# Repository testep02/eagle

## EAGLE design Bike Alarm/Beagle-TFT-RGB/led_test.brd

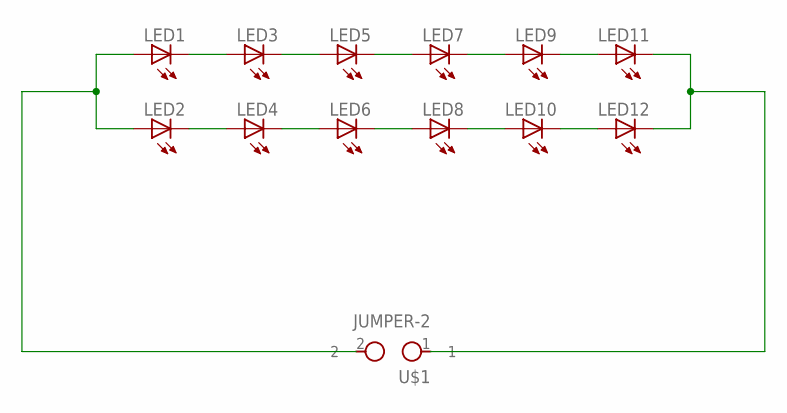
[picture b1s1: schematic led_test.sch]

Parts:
LED1, LED2, LED3, LED4, LED5, LED6, LED7, LED8, LED9, LED10, LED11, LED12: LEDCHIPLED_0603; CHIPLED_0603
U$1: JUMPER-2; 1X02

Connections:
LED+: LED1.A, LED2.A, U$1.2
LED-: LED11.C, LED12.C, U$1.1
unnamed: LED1.C, LED3.A
unnamed: LED3.C, LED5.A
unnamed: LED5.C, LED7.A
unnamed: LED7.C, LED9.A
unnamed: LED9.C, LED11.A
unnamed: LED10.C, LED12.A
unnamed: LED8.C, LED10.A
unnamed: LED6.C, LED8.A
unnamed: LED4.C, LED6.A
unnamed: LED2.C, LED4.A

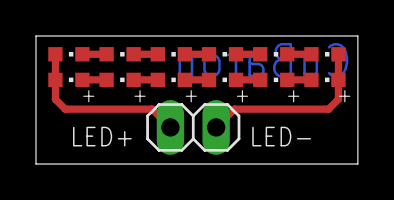
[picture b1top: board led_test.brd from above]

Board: 2 copper layers, 17.9 x 7.1 mm, 13 parts (0 on the bottom side), 12 nets.

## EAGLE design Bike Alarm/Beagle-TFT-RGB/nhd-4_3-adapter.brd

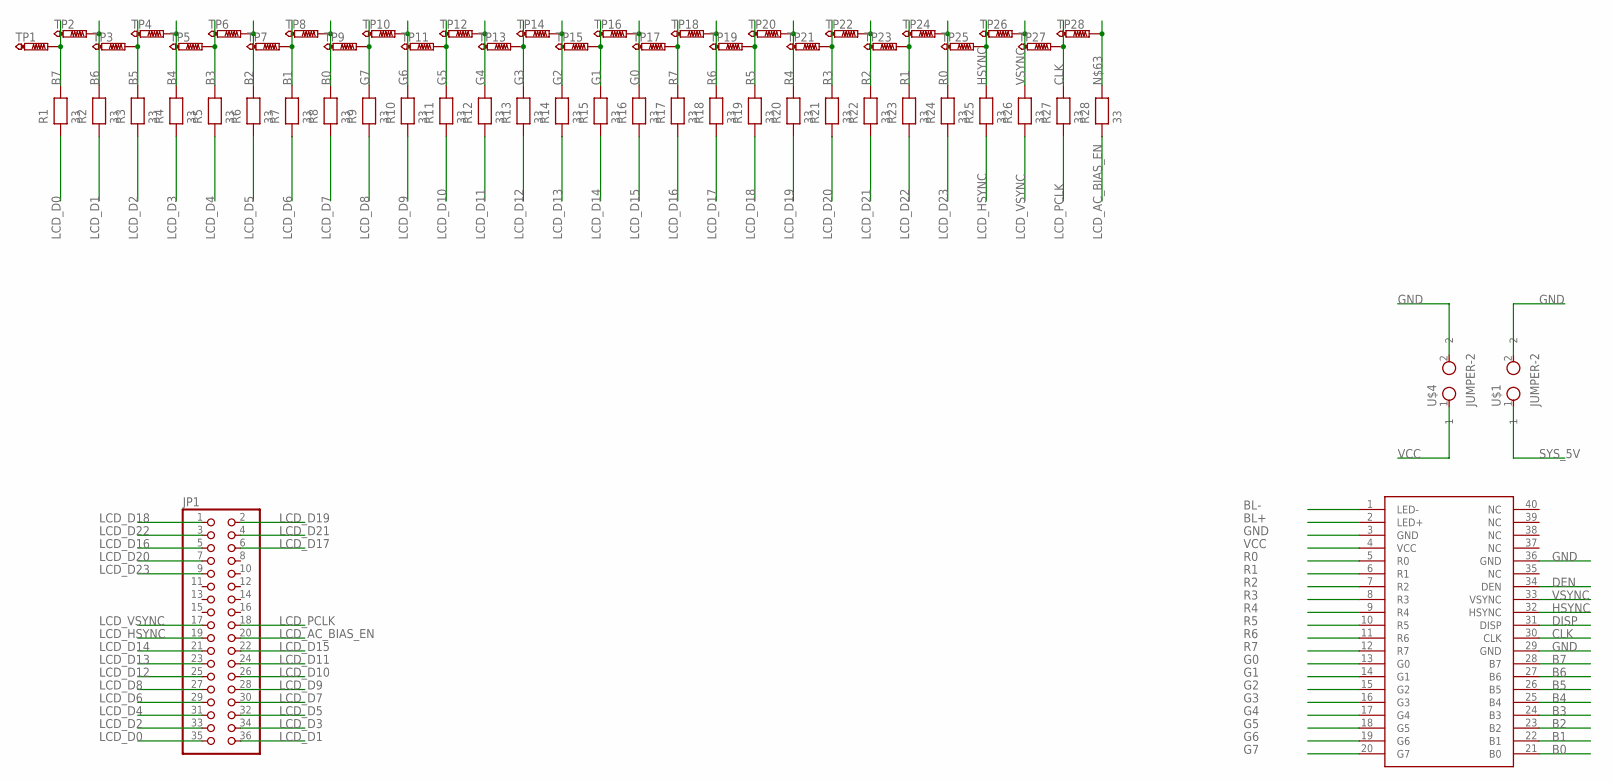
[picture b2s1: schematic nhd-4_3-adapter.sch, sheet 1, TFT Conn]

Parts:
JP1: PINHD-2X18_2.54; 2X18
R1, R2, R3, R4, R5, R6, R7, R8, R9, R10, R11, R12, R13, R14, R15, R16, R17, R18, R19, R20, R21, R22, R23, R24, R25, R26, R27, R28: 33; R0402
TFT1: NHD-4.3-480272EF-ATXL; 40-PIN_SMD
TP1, TP2, TP3, TP4, TP5, TP6, TP7, TP8, TP9, TP10, TP11, TP12, TP13, TP14, TP15, TP16, TP17, TP18, TP19, TP20, TP21, TP22, TP23, TP24, TP25, TP26, TP27, TP28: TESTPAD_PTR1TP06R; TESTPAD_TP06R
U$1, U$4: JUMPER-2; 1X02

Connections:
B0: R8.P$2, TFT1.21 (B0), TP8.TP
B1: R7.P$2, TFT1.22 (B1), TP7.TP
B2: R6.P$2, TFT1.23 (B2), TP6.TP
B3: R5.P$2, TFT1.24 (B3), TP5.TP
B4: R4.P$2, TFT1.25 (B4), TP4.TP
B5: R3.P$2, TFT1.26 (B5), TP3.TP
B6: R2.P$2, TFT1.27 (B6), TP2.TP
B7: R1.P$2, TFT1.28 (B7), TP1.TP
BL+: TFT1.2 (LED+); also elsewhere on the board
BL-: TFT1.1 (LED-); also elsewhere on the board
CLK: R27.P$2, TFT1.30 (CLK), TP27.TP
DEN: TFT1.34 (DEN)
DISP: TFT1.31 (DISP)
G0: R16.P$2, TFT1.13 (G0), TP16.TP
G1: R15.P$2, TFT1.14 (G1), TP15.TP
G2: R14.P$2, TFT1.15 (G2), TP14.TP
G3: R13.P$2, TFT1.16 (G3), TP13.TP
G4: R12.P$2, TFT1.17 (G4), TP12.TP
G5: R11.P$2, TFT1.18 (G5), TP11.TP
G6: R10.P$2, TFT1.19 (G6), TP10.TP
G7: R9.P$2, TFT1.20 (G7), TP9.TP
GND: TFT1.3 (GND), TFT1.29 (GND), TFT1.36 (GND), U$1.2, U$4.2; also elsewhere on the board
HSYNC: R25.P$2, TFT1.32 (HSYNC), TP25.TP
LCD_AC_BIAS_EN: JP1.20, R28.P$1
LCD_D0: JP1.35, R1.P$1
LCD_D1: JP1.36, R2.P$1
LCD_D2: JP1.33, R3.P$1
LCD_D3: JP1.34, R4.P$1
LCD_D4: JP1.31, R5.P$1
LCD_D5: JP1.32, R6.P$1
LCD_D6: JP1.29, R7.P$1
LCD_D7: JP1.30, R8.P$1
LCD_D8: JP1.27, R9.P$1
LCD_D9: JP1.28, R10.P$1
LCD_D10: JP1.26, R11.P$1
LCD_D11: JP1.24, R12.P$1
LCD_D12: JP1.25, R13.P$1
LCD_D13: JP1.23, R14.P$1
LCD_D14: JP1.21, R15.P$1
LCD_D15: JP1.22, R16.P$1
LCD_D16: JP1.5, R17.P$1
LCD_D17: JP1.6, R18.P$1
LCD_D18: JP1.1, R19.P$1
LCD_D19: JP1.2, R20.P$1
LCD_D20: JP1.7, R21.P$1
LCD_D21: JP1.4, R22.P$1
LCD_D22: JP1.3, R23.P$1
LCD_D23: JP1.9, R24.P$1
LCD_HSYNC: JP1.19, R25.P$1
LCD_PCLK: JP1.18, R27.P$1
LCD_VSYNC: JP1.17, R26.P$1
unnamed: R28.P$2, TP28.TP
R0: R24.P$2, TFT1.5 (R0), TP24.TP
R1: R23.P$2, TFT1.6 (R1), TP23.TP
R2: R22.P$2, TFT1.7 (R2), TP22.TP
R3: R21.P$2, TFT1.8 (R3), TP21.TP
R4: R20.P$2, TFT1.9 (R4), TP20.TP
R5: R19.P$2, TFT1.10 (R5), TP19.TP
R6: R18.P$2, TFT1.11 (R6), TP18.TP
R7: R17.P$2, TFT1.12 (R7), TP17.TP
SYS_5V: U$1.1; also elsewhere on the board
VCC: TFT1.4 (VCC), U$4.1; also elsewhere on the board
VSYNC: R26.P$2, TFT1.33 (VSYNC), TP26.TP

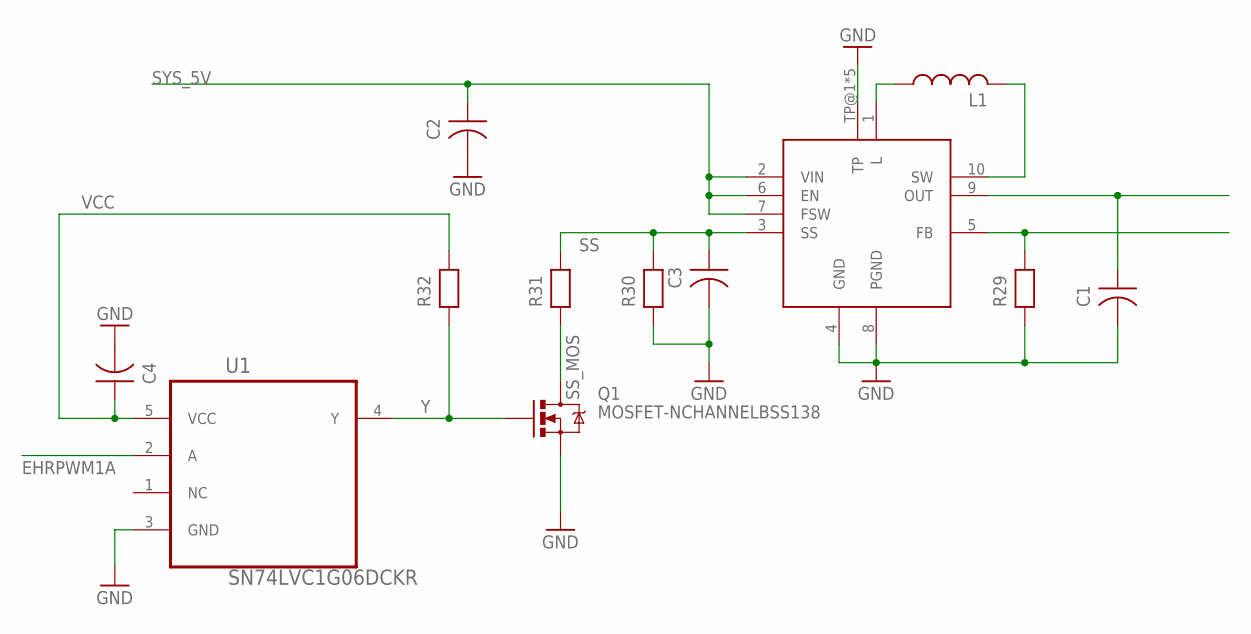
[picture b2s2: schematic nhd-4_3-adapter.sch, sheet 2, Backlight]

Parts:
C1, C2: PCAP0805LEVEL3; R0805
C3, C4: PCAP0603LEVEL3; R0603
L1: L-US; VLCF4018-2
Q1: MOSFET-NCHANNELBSS138; SOT23
R29, R30, R31, R32: PRES0603LEVEL3; R0603
U1: SN74LVC1G06DCKR; SOT65P210X110-5N
U$2: TPS61080; VSON-10

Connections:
BL+: C1.P$2, U$2.9 (OUT); also elsewhere on the board
BL-: R29.P$2, U$2.5 (FB); also elsewhere on the board
EHRPWM1A: U1.2 (A)
GND: C1.P$1, C2.P$1, C3.P$1, C4.P$1, Q1.2 (S), R29.P$1, R30.P$1, U1.3 (GND), U$2.4 (GND), U$2.8 (PGND), U$2.TP@1 (TP), U$2.TP@2 (TP), U$2.TP@3 (TP), U$2.TP@4 (TP), U$2.TP@5 (TP); also elsewhere on the board
L: L1.1, U$2.1 (L)
SS: C3.P$2, R30.P$2, R31.P$2, U$2.3 (SS)
SS_MOS: Q1.3 (D), R31.P$1
SW: L1.2, U$2.10 (SW)
SYS_5V: C2.P$2, U$2.2 (VIN), U$2.6 (EN), U$2.7 (FSW); also elsewhere on the board
VCC: C4.P$2, R32.P$2, U1.5 (VCC); also elsewhere on the board
Y: Q1.1 (G), R32.P$1, U1.4 (Y)

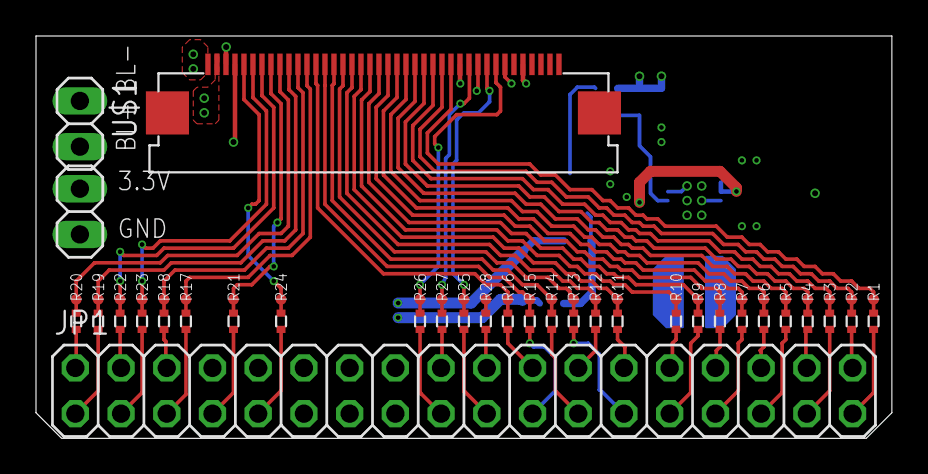
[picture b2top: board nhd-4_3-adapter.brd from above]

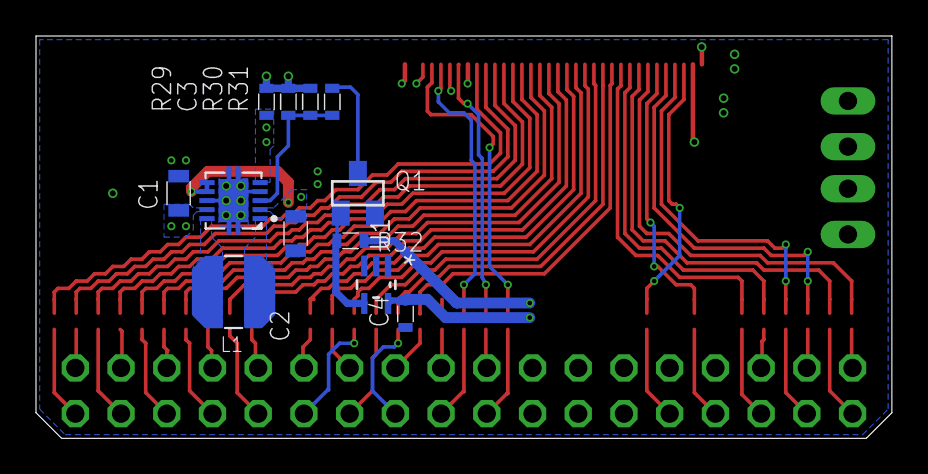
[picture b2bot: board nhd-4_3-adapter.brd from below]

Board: 4 copper layers, 47.5 x 22.4 mm, 72 parts (12 on the bottom side), 66 nets.

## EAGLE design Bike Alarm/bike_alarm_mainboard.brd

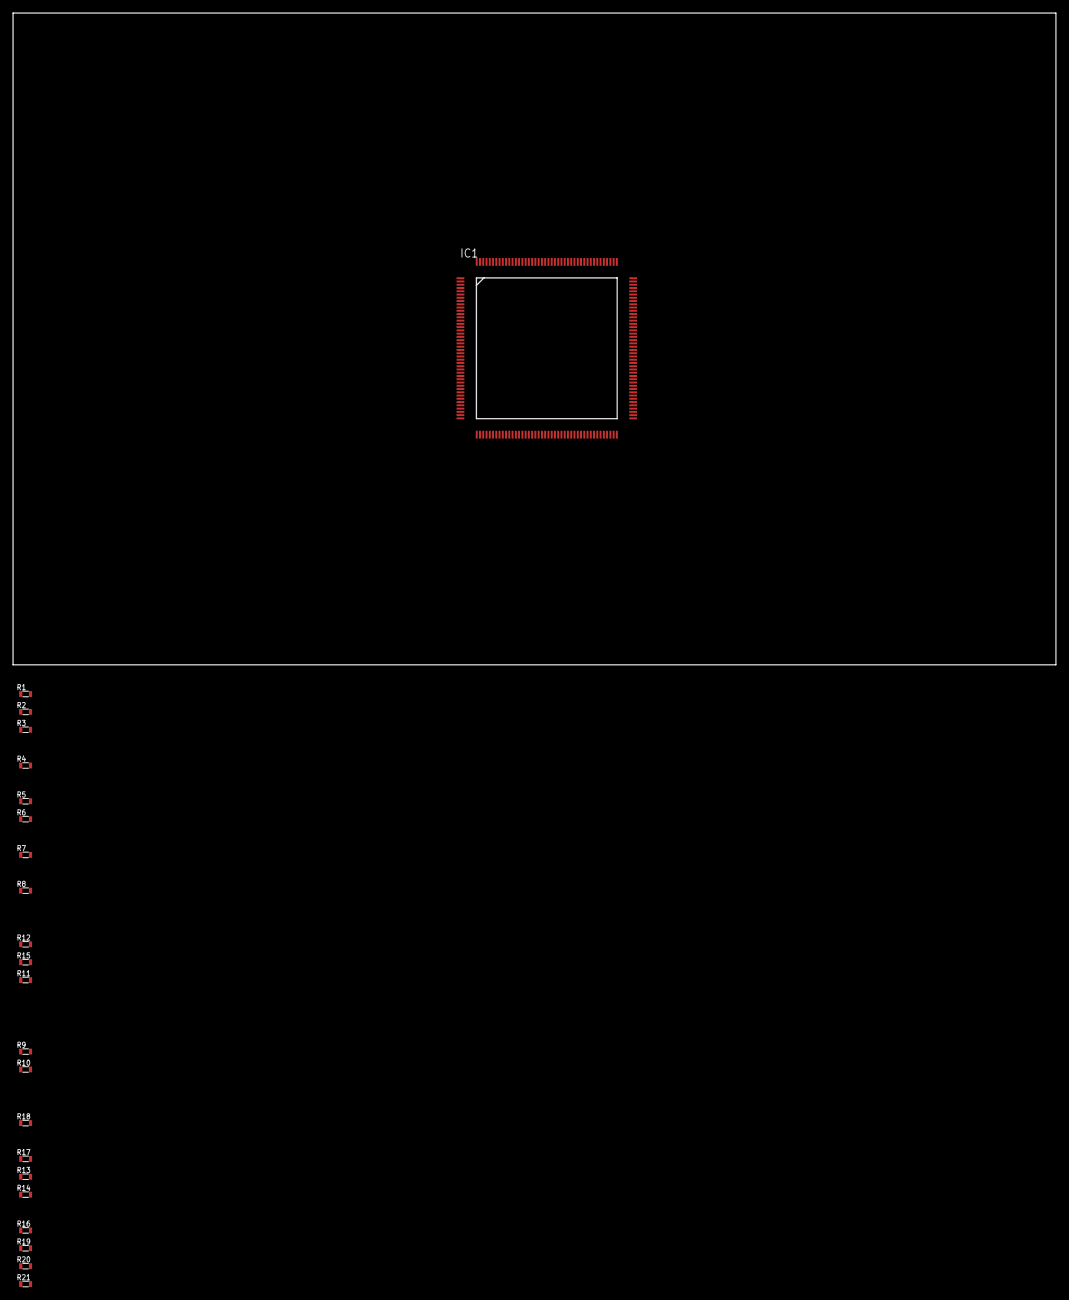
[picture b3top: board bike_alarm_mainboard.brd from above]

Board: 4 copper layers, 160.0 x 100.0 mm, 22 parts (0 on the bottom side), 2 nets, no tracks yet.

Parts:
IC1: STM32F439IIT_STM32F439IIT; STM32F439IIT_LQFP-176
R1, R2, R3, R4, R5, R6, R7, R8, R9, R10, R11, R12, R13, R14, R15, R16, R17, R18, R19, R20, R21: 0603L3

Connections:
VDD: IC1.15, IC1.23, IC1.36, IC1.49, IC1.72, IC1.82, IC1.91, IC1.103, IC1.114, IC1.127, IC1.136, IC1.149, IC1.159, IC1.172
VSS: IC1.14, IC1.22, IC1.61, IC1.71, IC1.90, IC1.102, IC1.113, IC1.126, IC1.135, IC1.148, IC1.158

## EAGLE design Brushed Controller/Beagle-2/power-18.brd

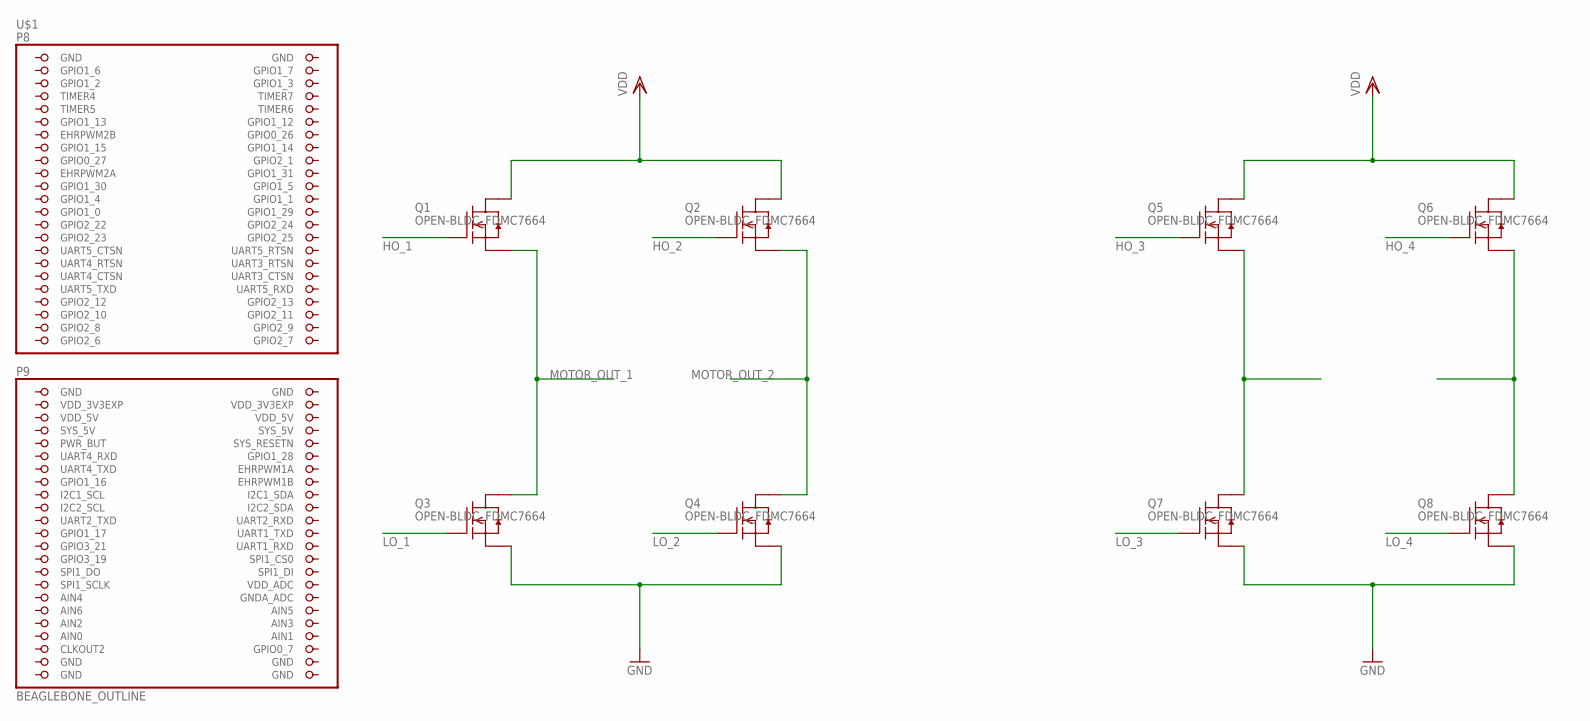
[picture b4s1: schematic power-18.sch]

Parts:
Q1, Q2, Q3, Q4, Q5, Q6, Q7, Q8: OPEN-BLDC_FDMC7664; OPEN-BLDC_MLP33
U$1: BEAGLEBONE_OUTLINE; BEAGLEBONE_SHIELD

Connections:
AIN0: U$1.85 (AIN0)
GND: Q3.123S (S), Q4.123S (S), Q7.123S (S), Q8.123S (S), U$1.1 (GND), U$1.2 (GND), U$1.47 (GND), U$1.48 (GND), U$1.89 (GND), U$1.90 (GND), U$1.91 (GND), U$1.92 (GND)
HO_1: Q1.4G (G)
HO_2: Q2.4G (G)
HO_3: Q5.4G (G)
HO_4: Q6.4G (G)
LO_1: Q3.4G (G)
LO_2: Q4.4G (G)
LO_3: Q7.4G (G)
LO_4: Q8.4G (G)
MOTOR_OUT_1: Q1.123S (S), Q3.5678D (D)
MOTOR_OUT_2: Q2.123S (S), Q4.5678D (D)
unnamed: Q6.123S (S), Q8.5678D (D)
unnamed: Q5.123S (S), Q7.5678D (D)
SYS_5V: U$1.53 (SYS_5V)
VDD: Q1.5678D (D), Q2.5678D (D), Q5.5678D (D), Q6.5678D (D)
VDD_3V3EXP: U$1.49 (VDD_3V3EXP), U$1.50 (VDD_3V3EXP)
VDD_5V: U$1.51 (VDD_5V), U$1.52 (VDD_5V)

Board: 2 copper layers, 9 parts (0 on the bottom side), 8 nets, no tracks yet.

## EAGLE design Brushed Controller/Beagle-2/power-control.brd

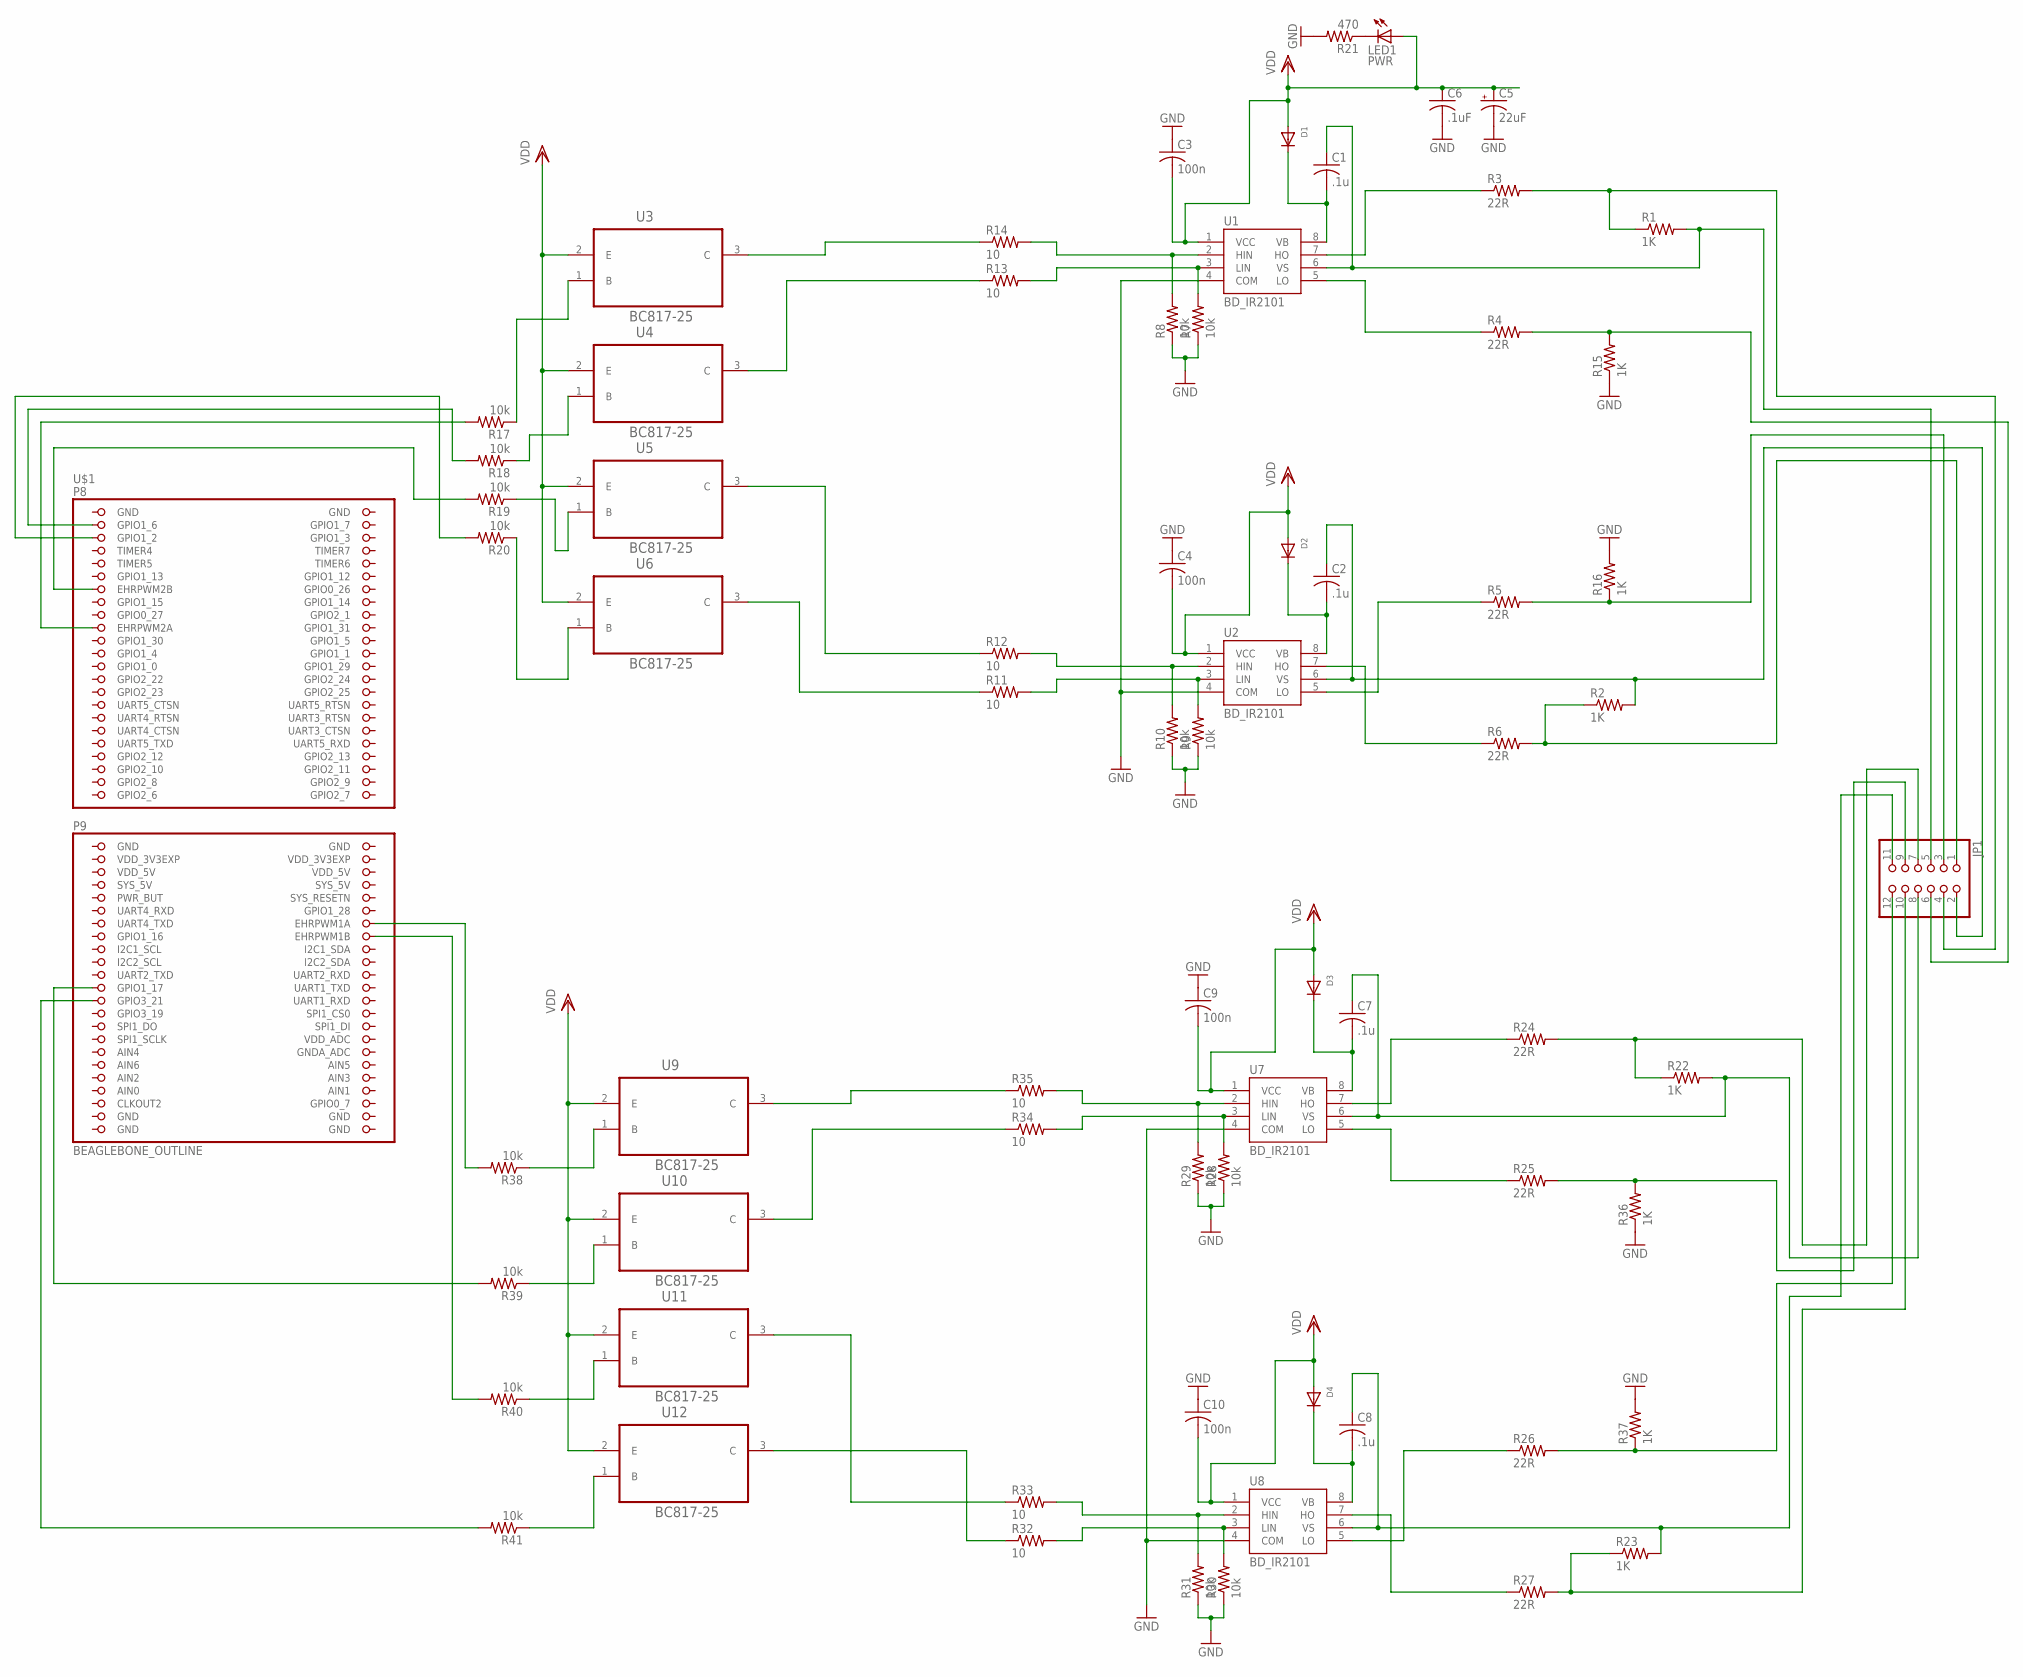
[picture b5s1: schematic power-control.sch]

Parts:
C1, C2, C7, C8: .1u; C0402
C3, C4, C9, C10: 100n; C0402
C5: 22uF; B/3528-21W
C6: .1uF; C0805
D1, D2, D3, D4: DIODESOD-523; SOD-523
JP1: PINHD-2X6_2.00; 2X06M
LED1: PWR; CHIP-LED0805
R1, R2, R15, R16, R22, R23, R36, R37: 1K; R0603
R3, R4, R5, R6, R24, R25, R26, R27: 22R; R0603
R7, R8, R9, R10, R17, R18, R19, R20, R28, R29, R30, R31, R38, R39, R40, R41: 10k; R0603
R11, R12, R13, R14, R32, R33, R34, R35: 10; R0603
R21: 470; R0201
U1, U2, U7, U8: BD_IR2101; SO8
U3, U4, U5, U6, U9, U10, U11, U12: BC817-25; SOT95P240X97-3N
U$1: BEAGLEBONE_OUTLINE; BEAGLEBONE_SHIELD

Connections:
AIN0: U$1.85 (AIN0)
GND: C3.1, C4.1, C5.-, C6.2, C9.1, C10.1, R7.1, R8.1, R9.1, R10.1, R15.1, R16.2, R21.2, R28.1, R29.1, R30.1, R31.1, R36.1, R37.2, U1.4 (COM), U2.4 (COM), U7.4 (COM), U8.4 (COM), U$1.1 (GND), U$1.2 (GND), U$1.47 (GND), U$1.48 (GND), U$1.89 (GND), U$1.90 (GND), U$1.91 (GND), U$1.92 (GND)
HO_1: R3.1, U1.7 (HO)
HO_2: R6.1, U2.7 (HO)
HO_3: R24.1, U7.7 (HO)
HO_4: R27.1, U8.7 (HO)
LO_1: R4.1, U1.5 (LO)
LO_2: R5.1, U2.5 (LO)
LO_3: R25.1, U7.5 (LO)
LO_4: R26.1, U8.5 (LO)
M1_G1_H: JP1.4, R1.1, R3.2
M1_G1_L: JP1.6, R4.2, R15.2
M1_G2_H: JP1.1, R2.1, R6.2
M1_G2_L: JP1.3, R5.2, R16.1
M2_G1_H: JP1.7, R22.1, R24.2
M2_G1_L: JP1.9, R25.2, R36.2
M2_G2_H: JP1.10, R23.1, R27.2
M2_G2_L: JP1.12, R26.2, R37.1
MOTOR_OUT_1: C1.1, JP1.5, R1.2, U1.6 (VS)
MOTOR_OUT_2: C2.1, JP1.2, R2.2, U2.6 (VS)
MOTOR_OUT_3: C7.1, JP1.8, R22.2, U7.6 (VS)
MOTOR_OUT_4: C8.1, JP1.11, R23.2, U8.6 (VS)
unnamed: R13.1, U4.3 (C)
unnamed: R11.1, U6.3 (C)
unnamed: R8.2, R14.2, U1.2 (HIN)
unnamed: R7.2, R13.2, U1.3 (LIN)
unnamed: R10.2, R12.2, U2.2 (HIN)
unnamed: R9.2, R11.2, U2.3 (LIN)
unnamed: C1.2, D1.K (C), U1.8 (VB)
unnamed: C2.2, D2.K (C), U2.8 (VB)
unnamed: R12.1, U5.3 (C)
unnamed: R19.2, U$1.13 (EHRPWM2B)
unnamed: R14.1, U3.3 (C)
unnamed: R18.2, U$1.3 (GPIO1_6)
unnamed: R20.2, U$1.5 (GPIO1_2)
unnamed: R38.2, U$1.60 (EHRPWM1A)
unnamed: R40.2, U$1.62 (EHRPWM1B)
unnamed: R39.2, U$1.69 (GPIO1_17)
unnamed: R17.1, U3.1 (B)
unnamed: R18.1, U4.1 (B)
unnamed: R19.1, U5.1 (B)
unnamed: R17.2, U$1.19 (EHRPWM2A)
unnamed: R20.1, U6.1 (B)
unnamed: LED1.C, R21.1
unnamed: R29.2, R35.2, U7.2 (HIN)
unnamed: R28.2, R34.2, U7.3 (LIN)
unnamed: R41.2, U$1.71 (GPIO3_21)
unnamed: R31.2, R33.2, U8.2 (HIN)
unnamed: R30.2, R32.2, U8.3 (LIN)
unnamed: C7.2, D3.K (C), U7.8 (VB)
unnamed: C8.2, D4.K (C), U8.8 (VB)
unnamed: R34.1, U10.3 (C)
unnamed: R35.1, U9.3 (C)
unnamed: R32.1, U12.3 (C)
unnamed: R33.1, U11.3 (C)
unnamed: R38.1, U9.1 (B)
unnamed: R39.1, U10.1 (B)
unnamed: R40.1, U11.1 (B)
unnamed: R41.1, U12.1 (B)
SYS_5V: U$1.53 (SYS_5V)
VDD: C3.2, C4.2, C5.+, C6.1, C9.2, C10.2, D1.A, D2.A, D3.A, D4.A, LED1.A, U1.1 (VCC), U2.1 (VCC), U3.2 (E), U4.2 (E), U5.2 (E), U6.2 (E), U7.1 (VCC), U8.1 (VCC), U9.2 (E), U10.2 (E), U11.2 (E), U12.2 (E)
VDD_3V3EXP: U$1.49 (VDD_3V3EXP), U$1.50 (VDD_3V3EXP)
VDD_5V: U$1.51 (VDD_5V), U$1.52 (VDD_5V)

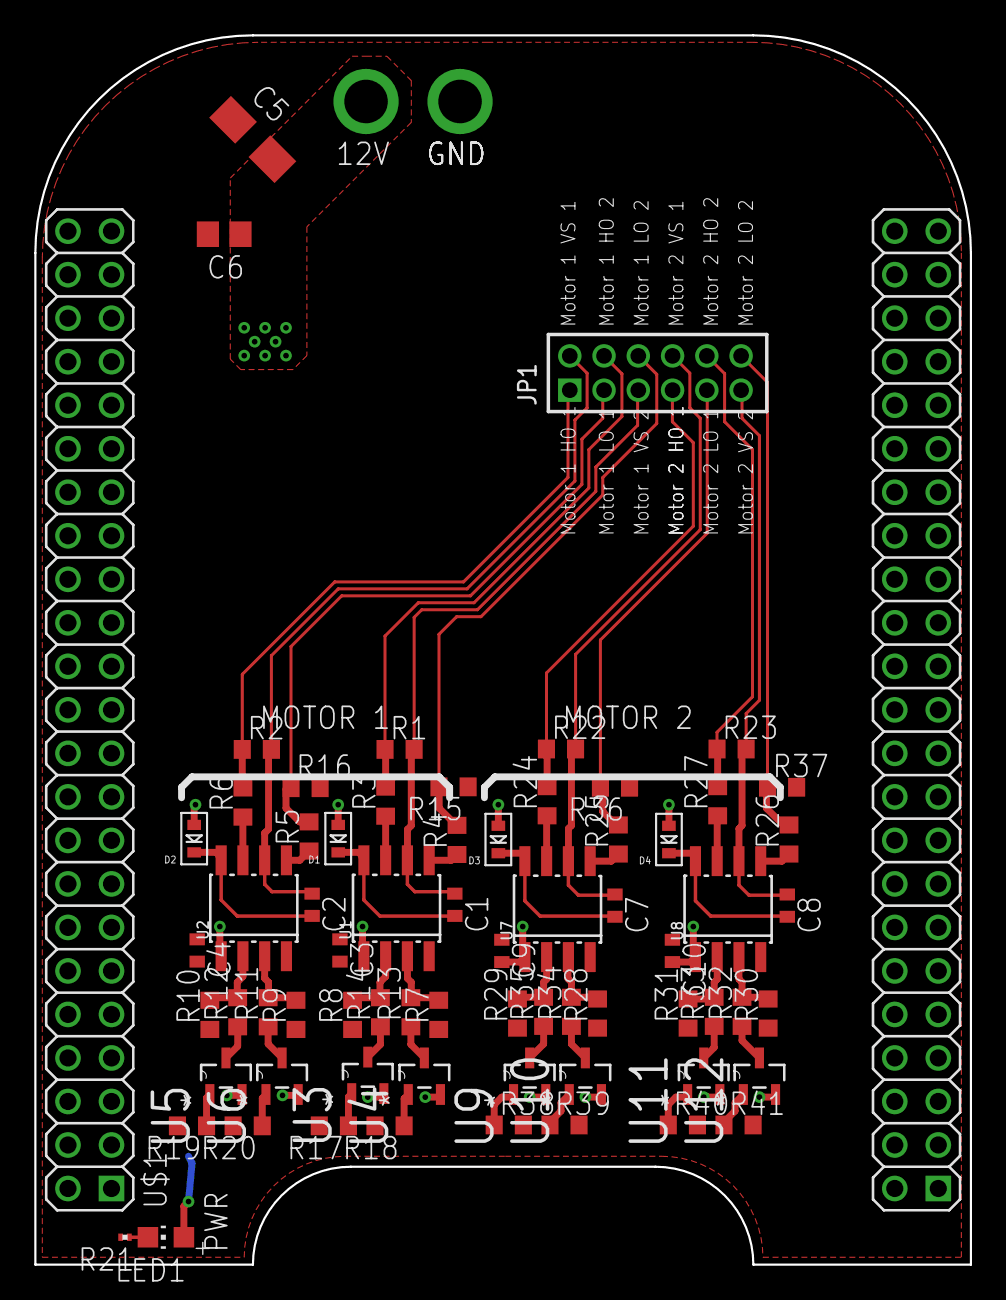
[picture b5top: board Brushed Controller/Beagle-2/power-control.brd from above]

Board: 2 copper layers, 54.6 x 71.8 mm, 70 parts (0 on the bottom side), 61 nets.

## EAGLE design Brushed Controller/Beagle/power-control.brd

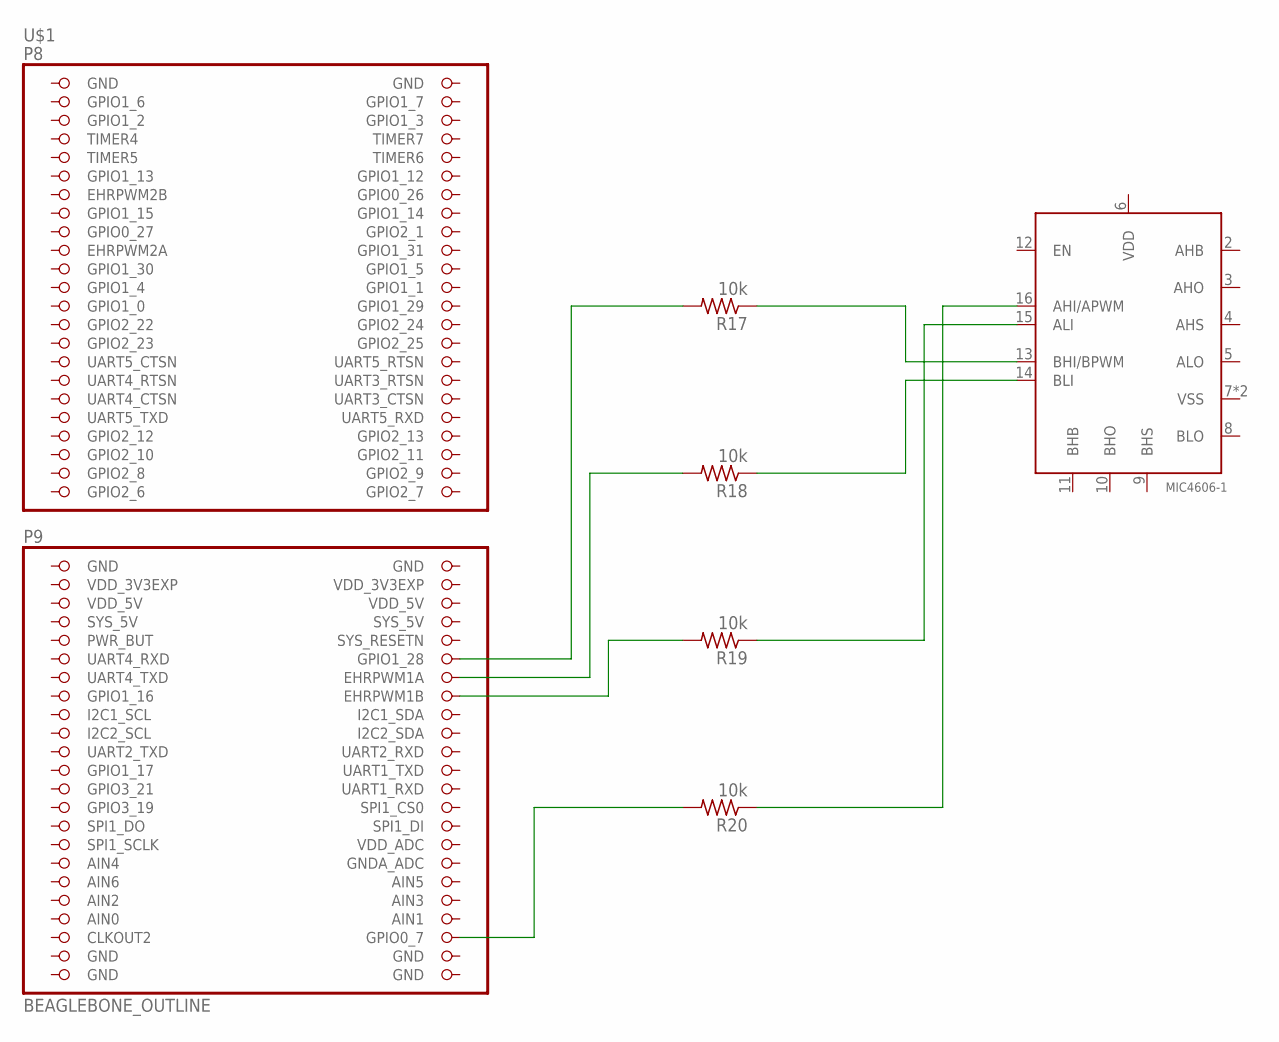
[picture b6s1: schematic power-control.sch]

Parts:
MD1: MIC4606-1; QFN44-16LD-PL-2
R17, R18, R19, R20: 10k; R0603
U$1: BEAGLEBONE_OUTLINE; BEAGLEBONE_SHIELD

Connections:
AIN0: U$1.85 (AIN0)
GND: U$1.1 (GND), U$1.2 (GND), U$1.47 (GND), U$1.48 (GND), U$1.89 (GND), U$1.90 (GND), U$1.91 (GND), U$1.92 (GND)
unnamed: MD1.16 (AHI/APWM), R20.1
unnamed: MD1.15 (ALI), R19.1
unnamed: R19.2, U$1.62 (EHRPWM1B)
unnamed: R17.2, U$1.58 (GPIO1_28)
unnamed: R18.2, U$1.60 (EHRPWM1A)
unnamed: MD1.14 (BLI), R18.1
unnamed: MD1.13 (BHI/BPWM), R17.1
unnamed: R20.2, U$1.88 (GPIO0_7)
SYS_5V: U$1.53 (SYS_5V)
VDD_3V3EXP: U$1.49 (VDD_3V3EXP), U$1.50 (VDD_3V3EXP)
VDD_5V: U$1.51 (VDD_5V), U$1.52 (VDD_5V)

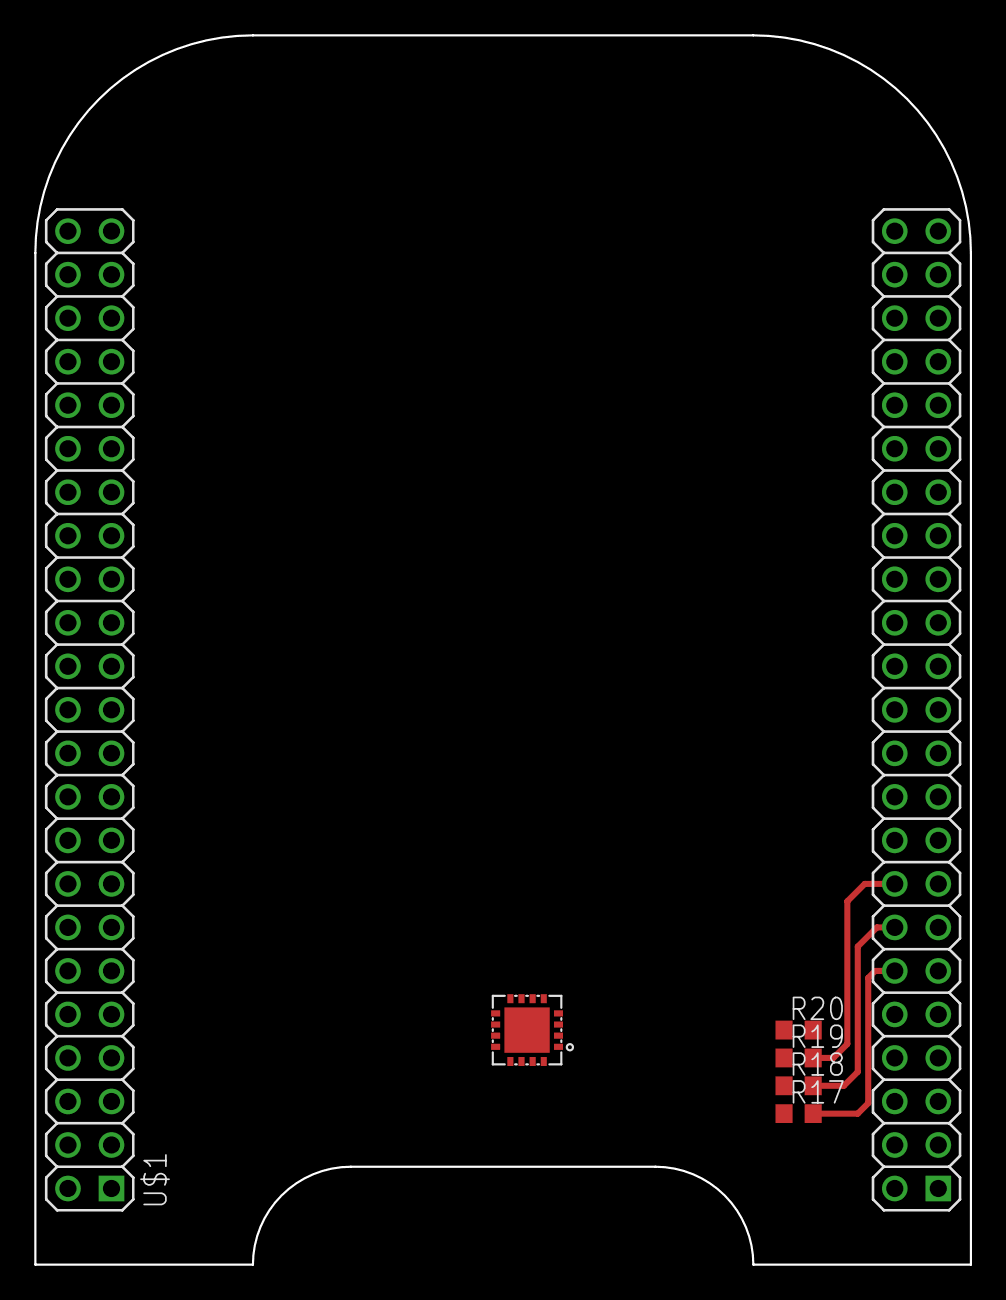
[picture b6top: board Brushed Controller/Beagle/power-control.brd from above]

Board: 4 copper layers, 54.6 x 71.8 mm, 6 parts (0 on the bottom side), 11 nets.

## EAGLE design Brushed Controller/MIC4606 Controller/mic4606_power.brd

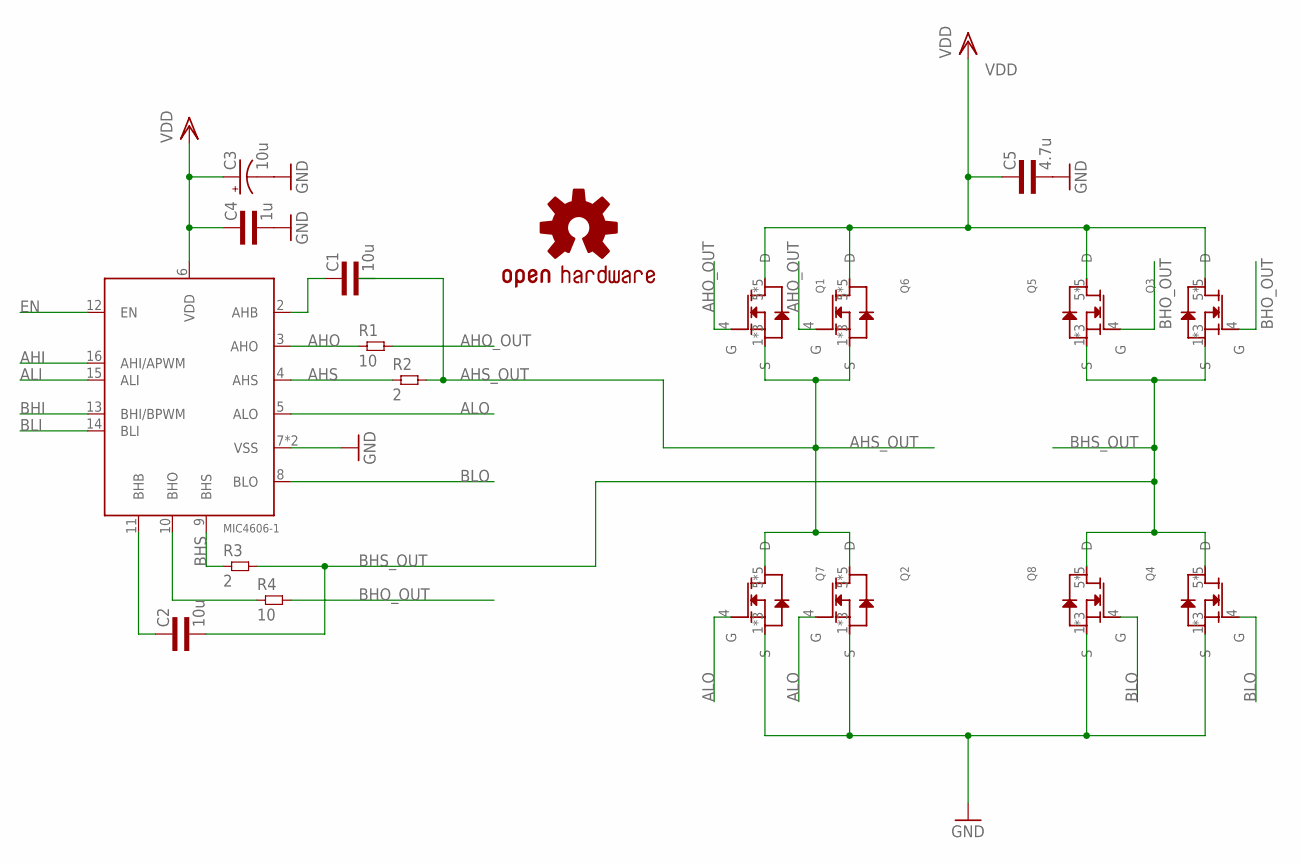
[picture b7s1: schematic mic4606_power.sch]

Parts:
C1, C2: 10u; 0805L3
C3: 10u; E1,8-4
C4: 1u; 0603L3
C5: 4.7u; 0805L3
LOGO1: OSHW-LOGOM; OSHW-LOGO-M
MD1: MIC4606-1; QFN44-16LD-PL-2
Q1, Q2, Q3, Q4, Q5, Q6, Q7, Q8: CSD18540Q5B; Q5B
R1, R4: 10; 0805L3
R2, R3: 2; 0805L3

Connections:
AHI: MD1.16 (AHI/APWM)
AHO: MD1.3 (AHO), R1.1
AHO_OUT: Q1.4 (G), Q6.4 (G), R1.2
AHS: MD1.4 (AHS), R2.1
AHS_OUT: C1.2, Q1.1 (S), Q1.2 (S), Q1.3 (S), Q2.5 (D), Q2.6 (D), Q2.7 (D), Q2.8 (D), Q2.9 (D), Q6.1 (S), Q6.2 (S), Q6.3 (S), Q7.5 (D), Q7.6 (D), Q7.7 (D), Q7.8 (D), Q7.9 (D), R2.2
ALI: MD1.15 (ALI)
ALO: MD1.5 (ALO), Q2.4 (G), Q7.4 (G)
BHI: MD1.13 (BHI/BPWM)
BHO: MD1.10 (BHO), R4.1
BHO_OUT: Q3.4 (G), Q5.4 (G), R4.2
BHS: MD1.9 (BHS), R3.1
BHS_OUT: C2.2, Q3.1 (S), Q3.2 (S), Q3.3 (S), Q4.5 (D), Q4.6 (D), Q4.7 (D), Q4.8 (D), Q4.9 (D), Q5.1 (S), Q5.2 (S), Q5.3 (S), Q8.5 (D), Q8.6 (D), Q8.7 (D), Q8.8 (D), Q8.9 (D), R3.2
BLI: MD1.14 (BLI)
BLO: MD1.8 (BLO), Q4.4 (G), Q8.4 (G)
EN: MD1.12 (EN)
GND: C3.-, C4.P$2 (2), C5.2, MD1.7 (VSS), MD1.TP (VSS), Q2.1 (S), Q2.2 (S), Q2.3 (S), Q4.1 (S), Q4.2 (S), Q4.3 (S), Q7.1 (S), Q7.2 (S), Q7.3 (S), Q8.1 (S), Q8.2 (S), Q8.3 (S)
unnamed: C1.1, MD1.2 (AHB)
unnamed: C2.1, MD1.11 (BHB)
VDD: C3.+, C4.P$1 (1), C5.1, MD1.6 (VDD), Q1.5 (D), Q1.6 (D), Q1.7 (D), Q1.8 (D), Q1.9 (D), Q3.5 (D), Q3.6 (D), Q3.7 (D), Q3.8 (D), Q3.9 (D), Q5.5 (D), Q5.6 (D), Q5.7 (D), Q5.8 (D), Q5.9 (D), Q6.5 (D), Q6.6 (D), Q6.7 (D), Q6.8 (D), Q6.9 (D)

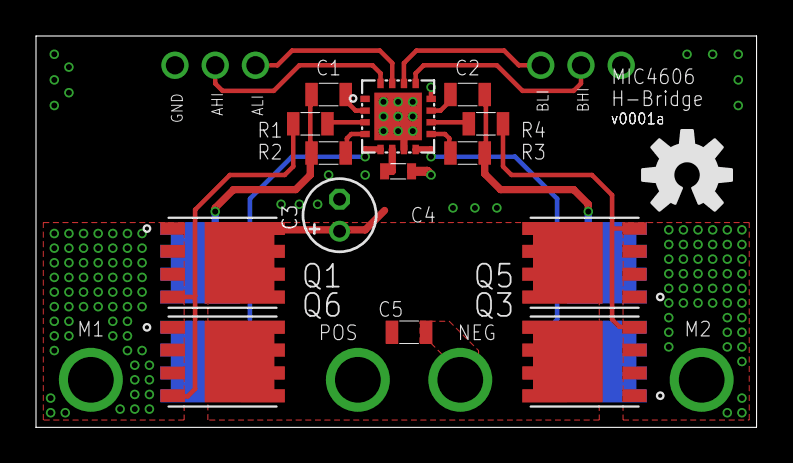
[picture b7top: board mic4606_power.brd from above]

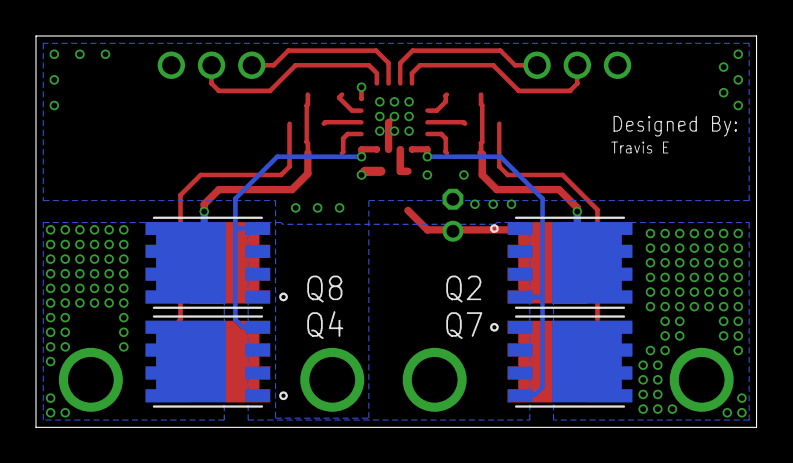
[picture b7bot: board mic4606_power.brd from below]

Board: 2 copper layers, 40.0 x 21.7 mm, 19 parts (4 on the bottom side), 14 nets.

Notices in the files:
parts and their libraries:
SparkFun-DiscreteSemi: Licensing: CC v3.0 Share-Alike You are welcome to use this library for commercial purposes.
